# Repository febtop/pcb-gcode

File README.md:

# pcb-gcode
pcb-gcode plugin for eagle cad including profile for Optimus

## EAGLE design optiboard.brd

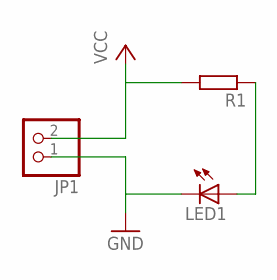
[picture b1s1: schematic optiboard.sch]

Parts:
JP1: PINHD-1X2; 1X02
LED1: LED3MM
R1: R-EU_0207/10; 0207/10

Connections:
GND: JP1.1, LED1.K (C)
unnamed: LED1.A, R1.1
VCC: JP1.2, R1.2

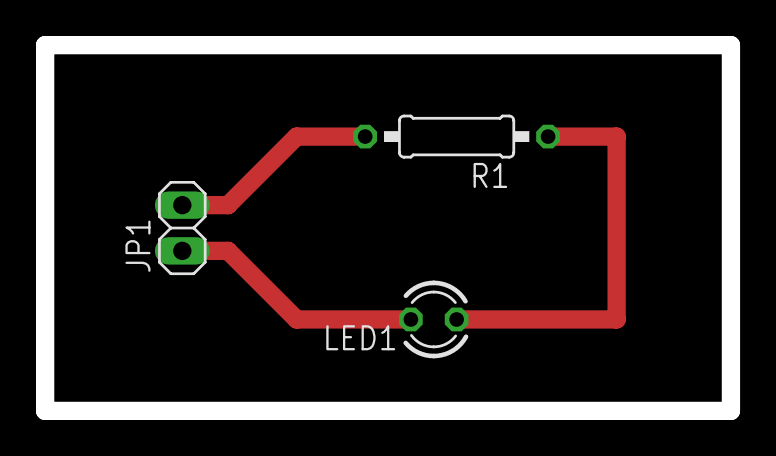
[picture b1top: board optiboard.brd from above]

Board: 2 copper layers, 38.1 x 20.3 mm, 3 parts (0 on the bottom side), 3 nets.

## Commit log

2017-06-09 added test eagle files
